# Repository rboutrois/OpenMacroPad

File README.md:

# OpenMacroPad
As its name suggests, it is an Open Hardware Macro Pad to access many computer shortcuts right under your palm

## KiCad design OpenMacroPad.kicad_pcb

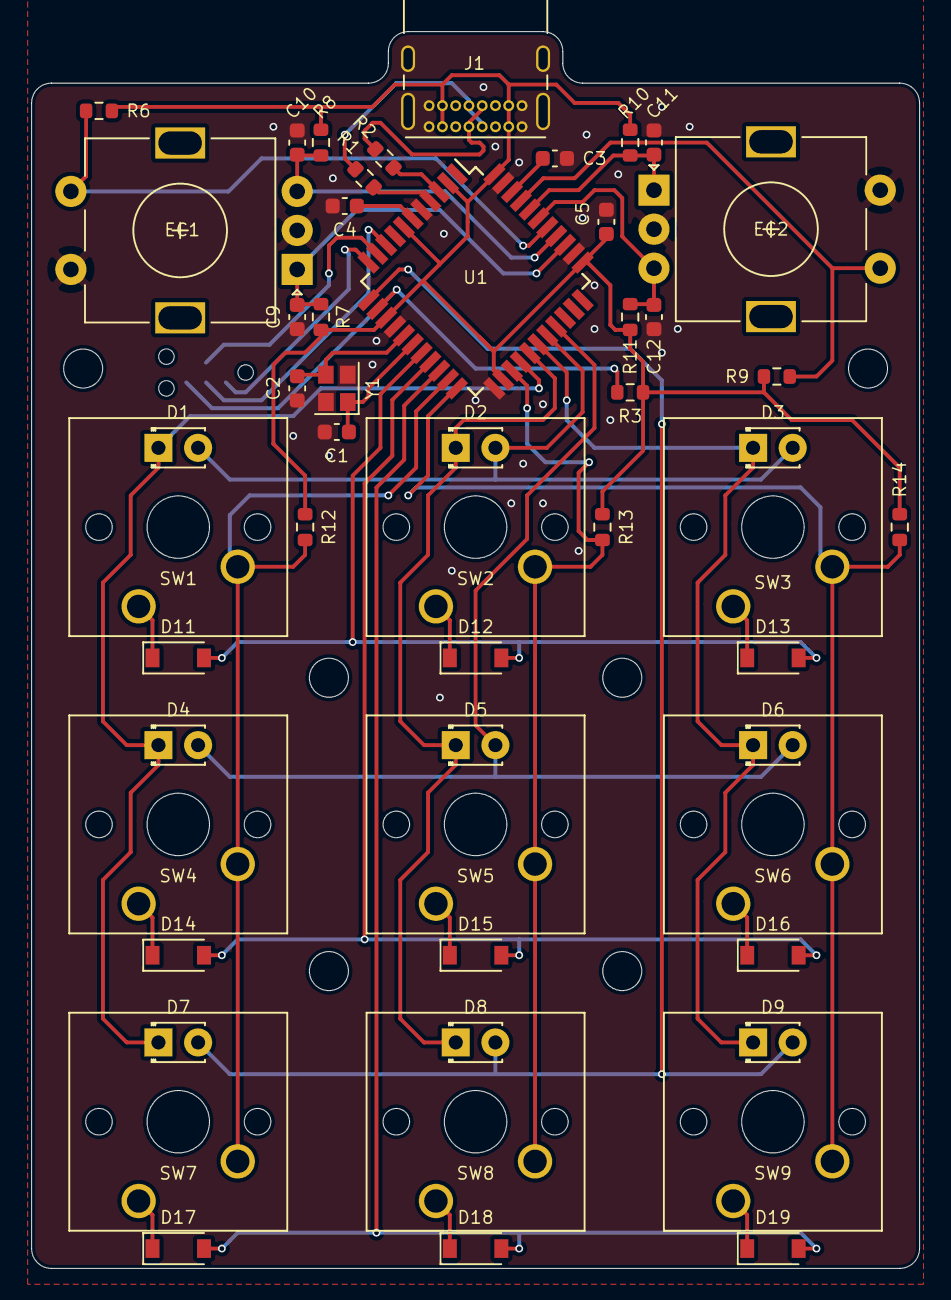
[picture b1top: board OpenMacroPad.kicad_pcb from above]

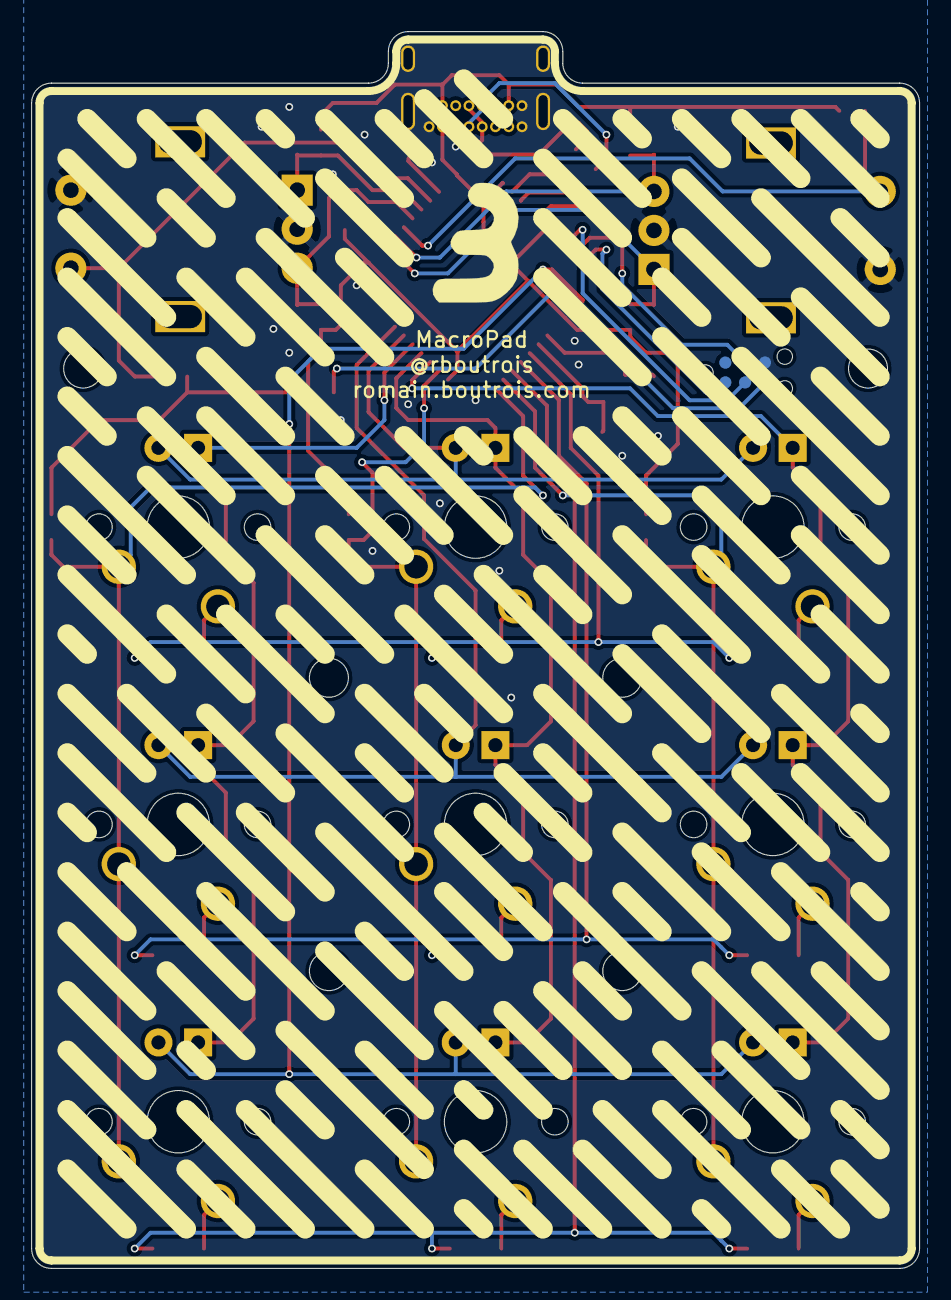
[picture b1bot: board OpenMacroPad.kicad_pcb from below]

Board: 2 copper layers, 56.9 x 79.2 mm, 61 parts (2 on the bottom side), 41 nets.

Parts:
C1, C2: 22pF; C_0603_1608Metric
C3, C5, C9, C10, C11, C12: 100nF; C_0603_1608Metric
C4: 1uF; C_0603_1608Metric
D1, D2, D3, D4, D5, D6, D7, D8, D9: LED; LED_D1.8mm_W3.3mm_H2.4mm
D11, D12, D13, D14, D15, D16, D17, D18, D19: DIODE; D_SOD-123
EC1, EC2: EC11E; RotaryEncoder_Alps_EC11E-Switch_Vertical_H20mm
H1, H2, H3, H4, H5, H6: MountingHole; MountingHole_2.5mm
J1: USB_C_Receptacle; USB_C_Receptacle_GCT_USB4085
J2: ICSP; Tag-Connect_TC2030-IDC-NL_2x03_P1.27mm_Vertical
R1, R2: 22R; R_0603_1608Metric
R3, R6, R7, R8, R9, R10, R11, R12, R13, R14: 10k; R_0603_1608Metric
SW1, SW2, SW3, SW4, SW5, SW6, SW7, SW8, SW9: SW_Push; SW_Cherry_MX_1.00u_PCB
U1: ATmega32U4-AU; TQFP-44_10x10mm_P0.8mm
Y1: 16MHz; Crystal_SMD_2520-4Pin_2.5x2.0mm
logo1: B3; logo

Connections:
D+: J1.A6, J1.B6, R1.1
D-: J1.A7, J1.B7, R2.2
EC1_A: C9.1, EC1.A, R7.1, U1.36
EC1_B: C10.2, EC1.B, R8.2, U1.37
EC1_SW: EC1.S1, R6.1, U1.38
EC2_A: C11.1, EC2.A, R10.1, U1.40
EC2_B: C12.2, EC2.B, R11.2, U1.39
EC2_SW: EC2.S1, R9.1, U1.41
GND: C1.1, C2.2, C3.2, C4.1, C5.1, C9.2, C10.1, C11.2, C12.1, EC1.C, EC1.S2, EC2.C, EC2.S2, J1.A1, J1.A12, J1.B1, J1.B12, J1.S1, J2.6, U1.5, U1.15, U1.23, U1.35, U1.43, Y1.2, Y1.4
LC1: D1.1, D4.1, D7.1, U1.26
LC2: D2.1, D5.1, D8.1, U1.27
LC3: D3.1, D6.1, D9.1, U1.28
LR1: D1.2, D2.2, D3.2, U1.29
LR2: D4.2, D5.2, D6.2, U1.30
LR3: D7.2, D8.2, D9.2, U1.12
MISO: J2.1, U1.11
MOSI: J2.4, U1.10
unnamed: C1.2, U1.17, Y1.1
unnamed: C2.1, U1.16, Y1.3
unnamed: C3.1, U1.42
unnamed: C4.2, U1.6
unnamed: D11.1, SW1.1
unnamed: D12.1, SW2.1
unnamed: D13.1, SW3.1
unnamed: D14.1, SW4.1
unnamed: D15.1, SW5.1
unnamed: D16.1, SW6.1
unnamed: D17.1, SW7.1
unnamed: D18.1, SW8.1
unnamed: D19.1, SW9.1
unnamed: R1.2, U1.4
unnamed: R2.1, U1.3
SC1: R12.1, SW1.2, SW4.2, SW7.2, U1.21
SC2: R13.1, SW2.2, SW5.2, SW8.2, U1.25
SC3: R14.1, SW3.2, SW6.2, SW9.2, U1.22
SCK: J2.3, U1.9
SR1: D11.2, D12.2, D13.2, U1.18
SR2: D14.2, D15.2, D16.2, U1.19
SR3: D17.2, D18.2, D19.2, U1.20
VBUS: C5.2, J1.A4, J1.A9, J1.B4, J1.B9, R3.2, R6.2, R7.2, R8.1, R9.2, R10.2, R11.1, R12.2, R13.2, R14.2, U1.2, U1.7, U1.14, U1.24, U1.34, U1.44
nRESET: J2.5, R3.1, U1.13

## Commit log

2021-03-11 First hardware version
2021-03-11 Add some pics
